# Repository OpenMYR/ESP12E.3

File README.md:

IoT Motor Hardware: Quad Servo
==============================
by OpenMYR

[OpenMYR Homepage](http://www.OpenMYR.com/)

Software by Brandon Brown and Kyle Berezin

Hardware design by Chris Adams

Hardware licensed under CERN Hardware License Version 1.2

Software licensed under MIT License

This repository is the source files for hardware designed to drive four servo motors with an ESP8266-based platform.

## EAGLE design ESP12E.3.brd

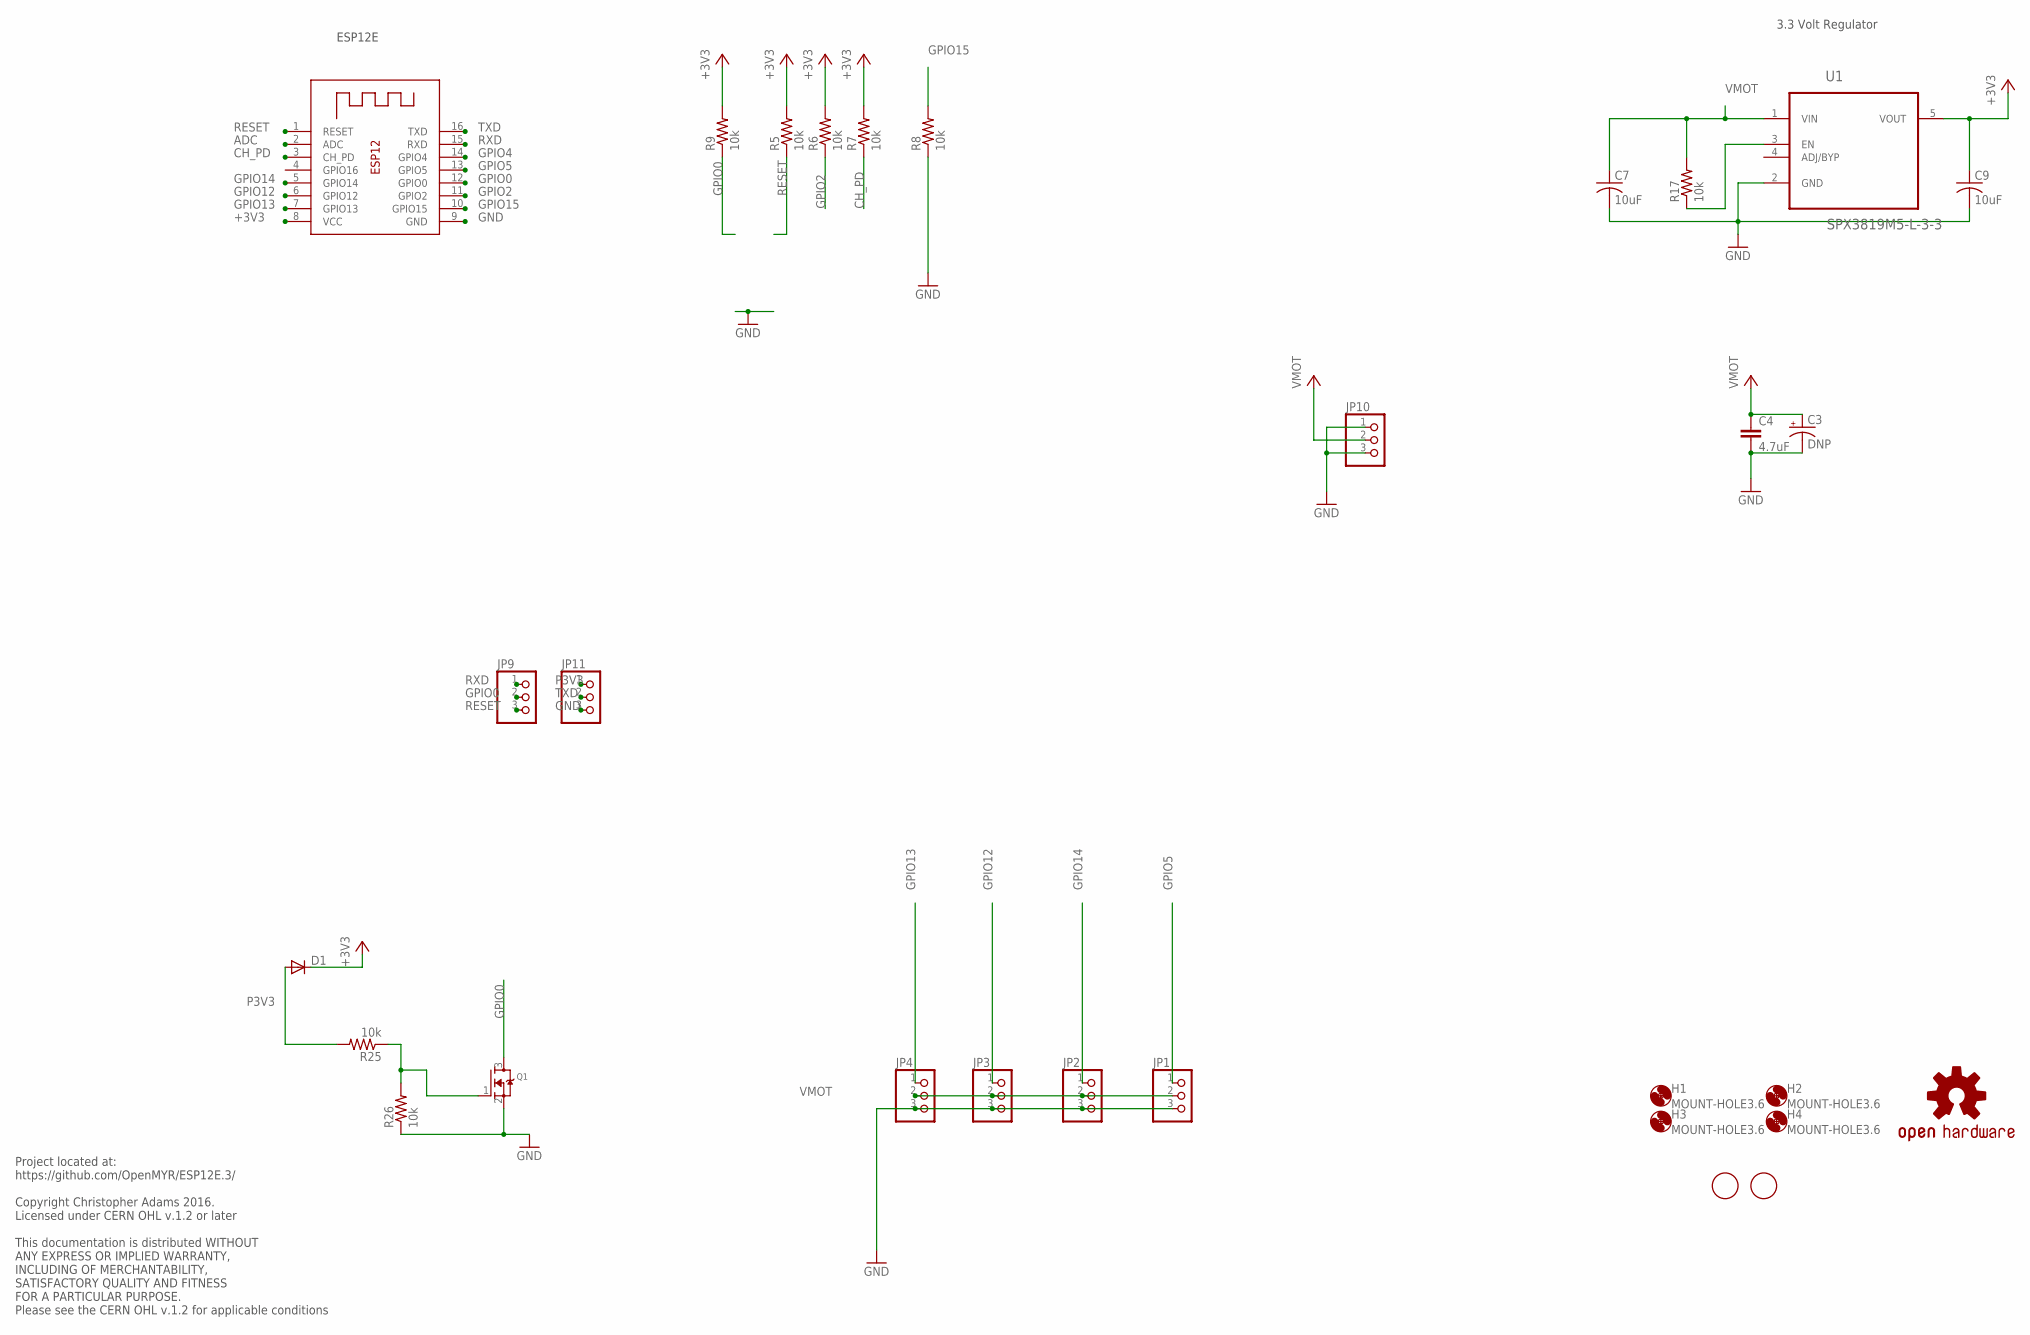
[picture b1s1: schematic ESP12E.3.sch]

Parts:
C3: DNP; E2-4
C4: 4.7uF; C0805
C7, C9: 10uF; C0603K
D1: DIODE-DO214AC; DO214AC
H1, H2, H3, H4: MOUNT-HOLE3.6; 3,6
JP1, JP2, JP3, JP4, JP9, JP10, JP11: PINHD-1X3; 1X03
LOGO1: OSHW-LOGOMINI; OSHW-LOGO-MINI
Q1: MOSFET-NREFLOW; SOT23
R5, R6, R7, R8, R9, R17, R25, R26: 10k; R0603
U1: SPX3819M5-L-3-3; SOT95P280X145-5N
U$3, U$4: FIDUCIAL; FIDUCIAL_1MM
X1: ESP-12

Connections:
+3V3: C9.1, D1.C, R5.2, R6.2, R7.2, R9.2, U1.5 (VOUT), X1.8 (VCC)
ADC: X1.2 (ADC)
CH_PD: R7.1, X1.3 (CH_PD)
GND: C3.-, C4.2, C7.2, C9.2, JP1.3, JP2.3, JP3.3, JP4.3, JP10.1, JP10.3, JP11.3, Q1.2 (S), R8.1, R26.1, U1.2 (GND), X1.9 (GND)
GPIO0: JP9.2, Q1.3 (D), R9.1, X1.12 (GPIO0)
GPIO2: R6.1, X1.11 (GPIO2)
GPIO4: X1.14 (GPIO4)
GPIO5: JP1.1, X1.13 (GPIO5)
GPIO12: JP3.1, X1.6 (GPIO12)
GPIO13: JP4.1, X1.7 (GPIO13)
GPIO14: JP2.1, X1.5 (GPIO14)
GPIO15: R8.2, X1.10 (GPIO15)
unnamed: R17.1, U1.3 (EN)
unnamed: Q1.1 (G), R25.1, R26.2
P3V3: D1.A, JP11.1, R25.2
RESET: JP9.3, R5.1, X1.1 (RESET)
RXD: JP9.1, X1.15 (RXD)
TXD: JP11.2, X1.16 (TXD)
VMOT: C3.+, C4.1, C7.1, JP1.2, JP2.2, JP3.2, JP4.2, JP10.2, R17.2, U1.1 (VIN)

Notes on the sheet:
3.3 Volt Regulator
ESP12E
Project located at: https://github.com/OpenMYR/ESP12E.3/ Copyright Christopher Adams 2016. Licensed under CERN OHL v.1.2 or later This documentation is distributed WITHOUT ANY EXPRESS OR IMPLIED WARRANTY, INCLUDING OF MERCHANTABILITY, SATISFACTORY QUALITY AND FITNESS FOR A PARTICULAR PURPOSE. Pleas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

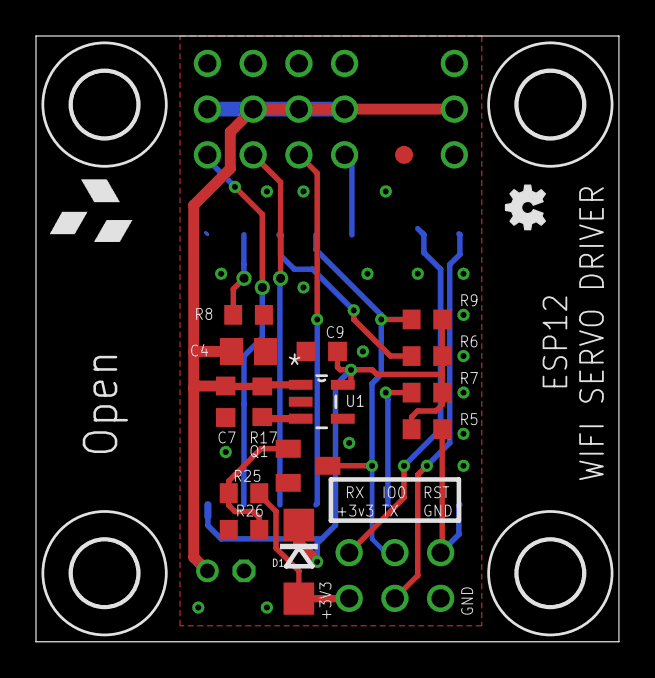
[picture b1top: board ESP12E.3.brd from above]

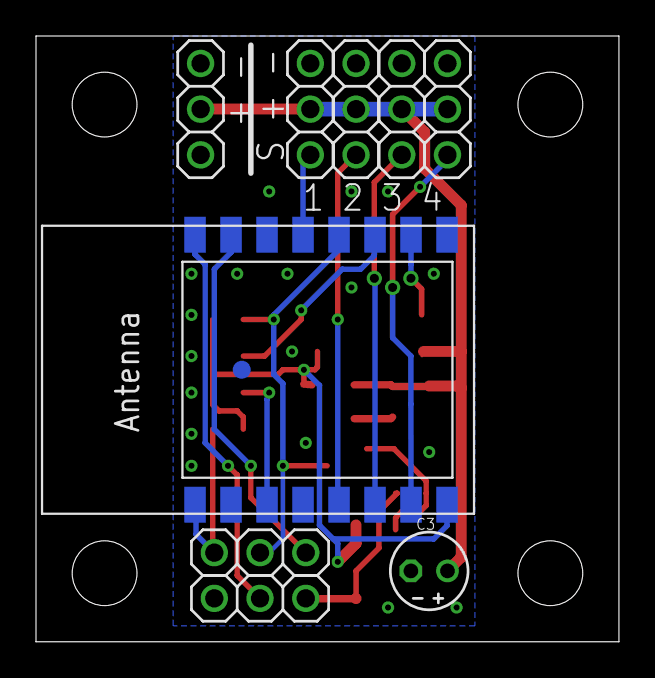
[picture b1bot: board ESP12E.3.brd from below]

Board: 2 copper layers, 32.4 x 33.7 mm, 30 parts (10 on the bottom side), 17 nets.

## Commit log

2016-04-10 :neckbeard: Added .gitattributes & .gitignore files
2016-04-10 First Commit
    Design 3:
    ESP12E with 4 GPIO driven Servo ports
2016-04-10 New Programming Header
    Modified loading method with 6 pin header.
    Flipped board in layout as most parts were on bottom layer.
    Board power now matches 3 pin servo cable.
2016-07-09 License Update
    Licensed under CERN OHL v.1.2 or later
2018-05-20 //Increased board size and added M3 mounting holes
2018-12-02 Start of ESP12.3 board transfer to KiCAD
2018-12-02 Update to net assignments and part updates.
